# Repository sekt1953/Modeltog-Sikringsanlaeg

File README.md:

# Modeltogs Sikringsanlæg

Sikrings anlæg for modeltog med DCC system, ESPHome &amp; Home Assistant

## [Datasheet](./Project/Datasheet/README.md#datasheet)

* [CanBus](./Project/Datasheet/README.md#canbus)
  * [ESPHome](./Project/Datasheet/README.md#esphome)
  * [Kabling](./Project/Datasheet/README.md#canbus-kabling)
  * [Videos](./Project/Datasheet/Kabeling/Canbus:Videos.md)
* [DCC](./Project/Datasheet/README.md#dcc)
  * [Kabling](./Project/Datasheet/README.md#dcc-kabling)
* [KiCad](./Project/Datasheet/README.md#kicad)
  * [Track impedans](./Project/Datasheet/README.md#track-impedans)
  * [Custom Symbol and Footprints](./Project/Datasheet/README.md#custom-symbol-and-footprints)
* [Parts:](./Project/Datasheet/README.md#parts)
  * [Semiconductor](./Project/Datasheet/README.md#semiconductor)
  * [Modules](./Project/Datasheet/README.md#modules)
  * [Stik](./Project/Datasheet/README.md#stik)

## [Libraries](./Project/libraries/README.md)

* [KiCad Libraries:](./Project/libraries/KiCad/)
  * [Modules Symboler](./Project/libraries/SEKT_Modules.kicad_sym)
  * [Modules Footprint](./Project/libraries/SEKT_Modules.pretty/)
* [FreeCAD 3D Step files:](./Project/libraries/README.md)
  * [Semiconductor](./Project/libraries/README.md#semiconductor)
  * [Modules](./Project/libraries/README.md#modules)
  * [Stik](./Project/libraries/README.md#stik)

## Projekter

* [Sporbesat](./Project/Sikring/Sporbesat/README.md)
  * Detektor kredsløb
    * [Beskrivelse af Sporbesat Detektor Diagram](./Project/Sikring/Sporbesat/Detektor/Beskrivelse.md)
    * KiCad Filer:
      * [Sporbesat-Detektor](./Project/Sikring/Sporbesat/Sikring_Sporbesat/Images/Sikring_Sporbesat-Sporbesat_Sensor.svg)
  * CANBUS
    * [CanBus og HomeAssistant](./Project/CANBUS/1_CanBus_og_HomeAssistant.md)
    * [CanBus med Output og svar](./Project/CANBUS/2_CanBus_med%20_Output_og_svar.md)
  * KiCAD
  * FreeCAD
  * ESPHome
  * Home Assistant
* Sporskifte styring
* Signal styring
* test

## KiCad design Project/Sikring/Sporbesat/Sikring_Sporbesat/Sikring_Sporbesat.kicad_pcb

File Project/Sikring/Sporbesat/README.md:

# Sikringsanlæg - Sporbesat

## 4 ports sporbesat detektor kredsløb

* Detektor kredsløb
  * [Beskrivelse af Sporbesat Detektor Diagram](./Detektor/Beskrivelse.md)
  * KiCad (Schmatic & PCB) filer:
    * [Sporbesat-Detektor.kicad_pro](../../KiCad/Sporbesat-Detektor/Sporbesat-Detektor.kicad_pro)
  * FreeCAD 3D modeller af komponenter:
    * [Datasheet Parts](../../Datasheet/README.md#parts)

## Transmitter

### KiCad (Schmatic & PCB)

* [Track impedans calculater](../../Datasheet/TrackImpedansCalculater.md)

### CanBus

#### [ESP32 CAN](https://esphome.io/components/canbus/esp32_can/)

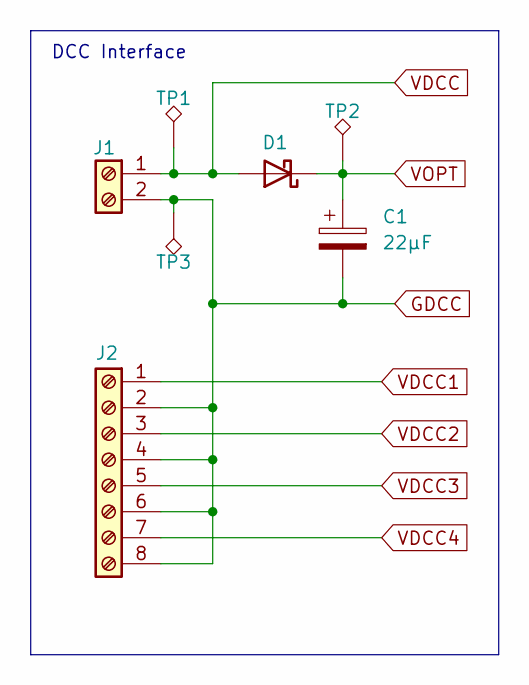
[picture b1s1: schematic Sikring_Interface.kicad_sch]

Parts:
C1: 22µF; CP_EIA-7343-43_Kemet-X
D1: Schottky, SMA, 30V, 1A; D_DO-214AC(SMA)
J1: Screw_Terminal_01x02; TerminalBlock_Phoenix_MKDS-1,5-2-5.08_1x02_P5.08mm_Horizont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
J2: Screw_Terminal_01x08; TerminalBlock_Phoenix_MKDS-1,5-8-5.08_1x08_P5.08mm_Horizont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
TP1: VDCC; TestPoint_Loop_D2.60mm_Drill1.4mm_Beaded
TP2: VOPT; TestPoint_Loop_D2.60mm_Drill1.4mm_Beaded
TP3: GDCC; TestPoint_Loop_D2.60mm_Drill1.4mm_Beaded

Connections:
GDCC: C1.2, J1.2, J2.2, J2.4, J2.6, J2.8, TP3.1 (1_1); also elsewhere on the board
VDCC: D1.2 (A), J1.1, TP1.1 (1_1); also elsewhere on the board
VDCC1: J2.1; also elsewhere on the board
VDCC2: J2.3; also elsewhere on the board
VDCC3: J2.5; also elsewhere on the board
VDCC4: J2.7; also elsewhere on the board
VOPT: C1.1, D1.1 (K), TP2.1 (1_1); also elsewhere on the board

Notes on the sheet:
DCC Interface

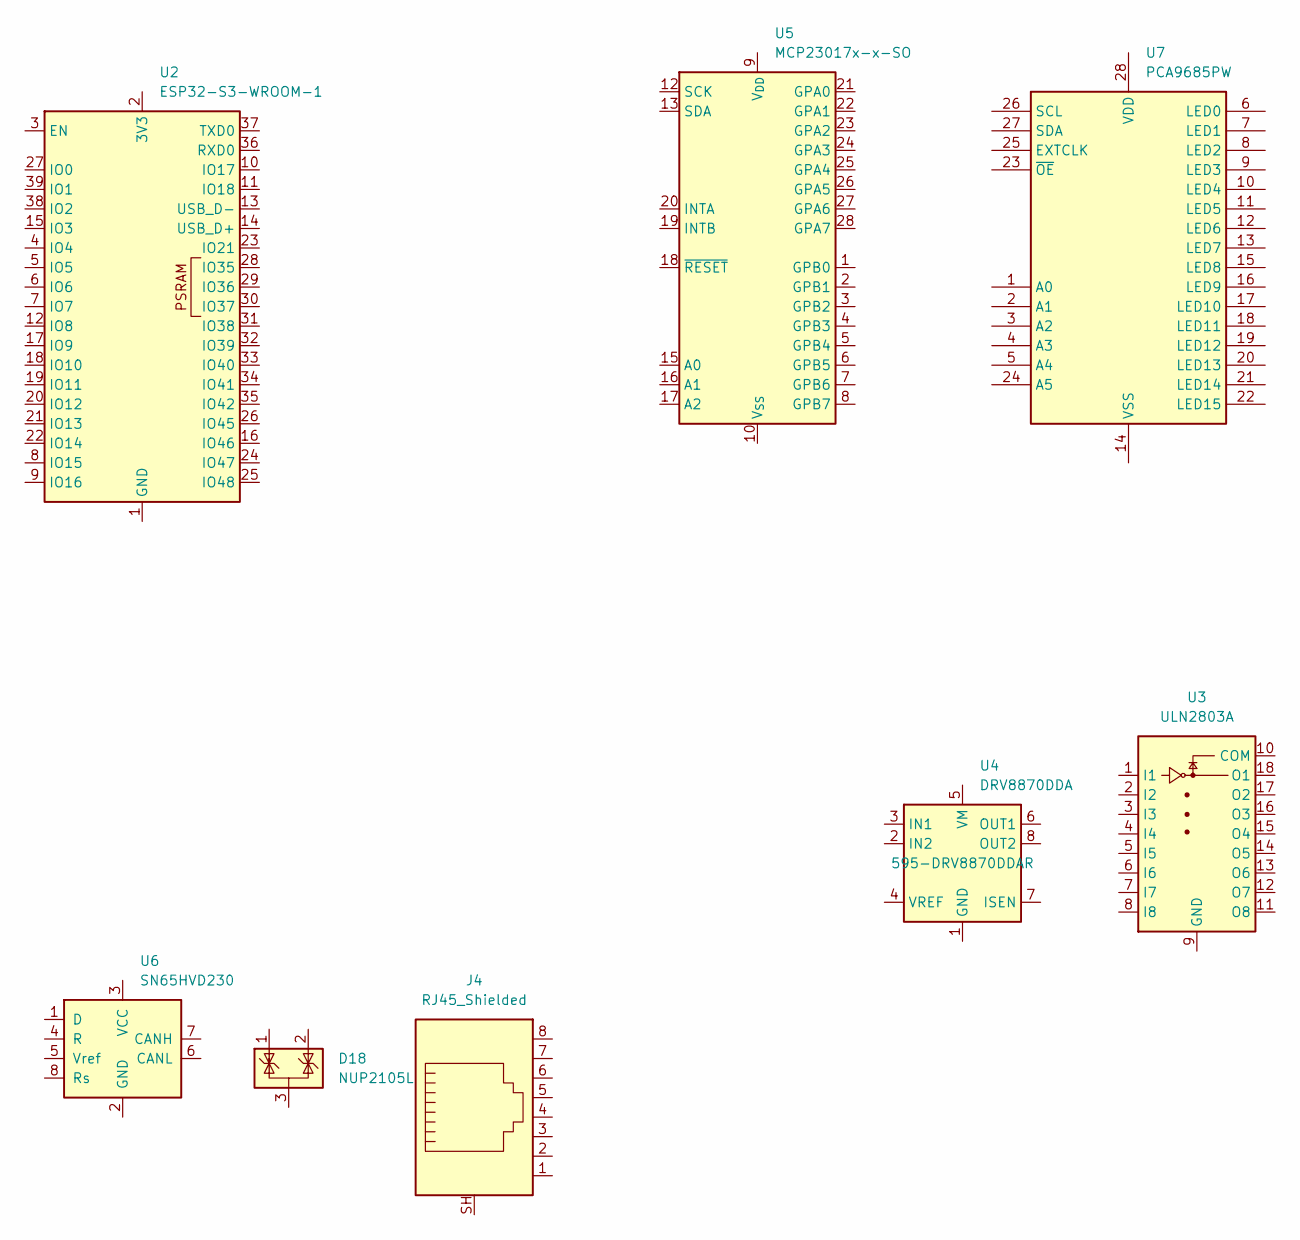
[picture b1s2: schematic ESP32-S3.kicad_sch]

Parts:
D18: NUP2105L; SOT-23; Mouser Part No 637-NUP2105L
J4: RJ45_Shielded; Mouser No: 490-CRJ009-ML4-TH
U2: ESP32-S3-WROOM-1
U3: ULN2803A; SOIC-18W_7.5x11.6mm_P1.27mm; Mouser Part No 595-ULN2803CDWR
U4: DRV8870DDA; Texas_HTSOP-8-1EP_3.9x4.9mm_P1.27mm_EP2.95x4.9mm_Mask2.4x3.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; Mouser Part No 595-DRV8870DDAR
U5: MCP23017x-x-SO; SOIC-28W_7.5x17.9mm_P1.27mm; Mouser No: 579-MCP23017-E/SO
U6: SN65HVD230; SOIC-8_3.9x4.9mm_P1.27mm; Mouser Part No 595-SN65HVD230DR
U7: PCA9685PW; TSSOP-28_4.4x9.7mm_P0.65mm; Mouser Part No 771-PCA9685PW,118

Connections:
unnamed: U2.1 (GND), U2.40 (GND), U2.41 (GND)
unnamed: U4.1 (GND), U4.9 (GND)

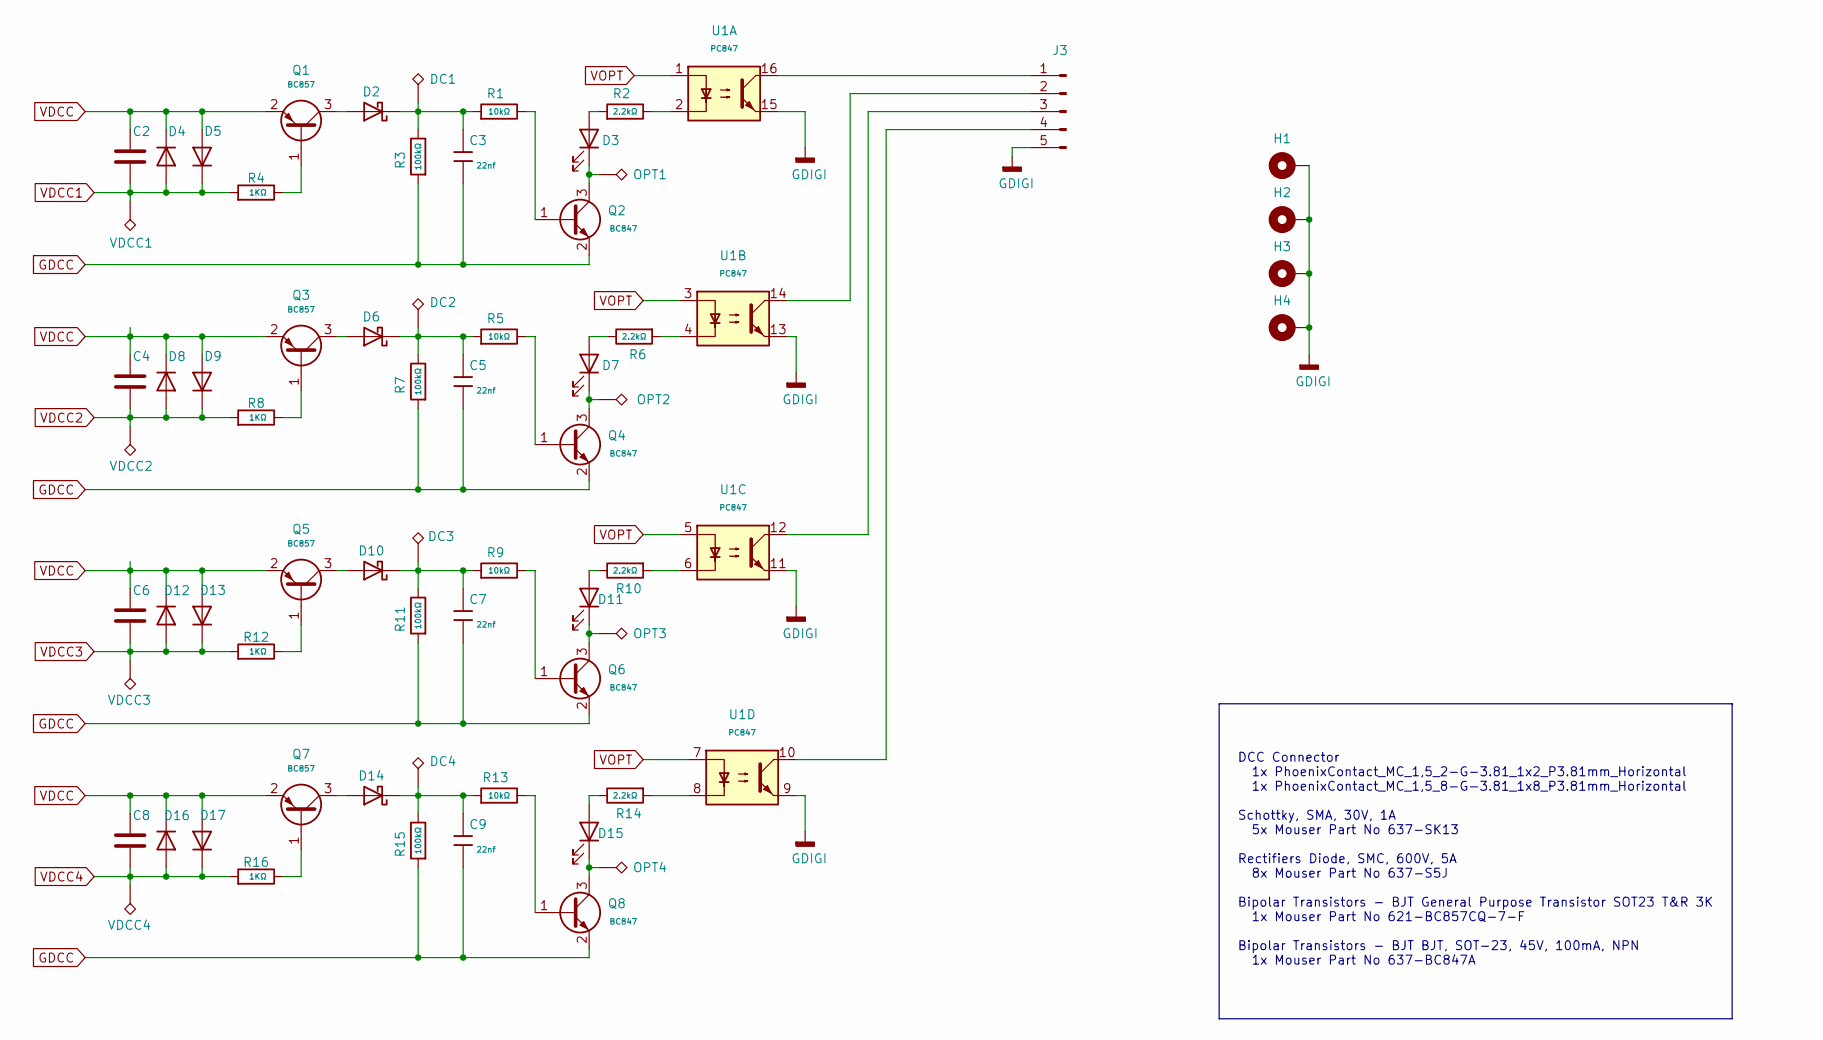
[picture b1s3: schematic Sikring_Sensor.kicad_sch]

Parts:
C2, C4, C6, C8: 100nF; C_1206_3216Metric
C3, C5, C7, C9: 22nf; C_1206_3216Metric; Voltage Rated 100V; Tolerance ±10%; Part CL21B474KBFNNNE; LCSC C13967
D2, D6, D10, D14: Schottky, SMA, 30V, 1A; D_DO-214AC(SMA)
D3, D7, D11, D15: LED; LED_0805_2012Metric
D4, D5, D8, D9, D12, D13, D16, D17: S5A; D_SMC(DO-214AB)
H1, H2, H3, H4: MountingHole_Pad; MountingHole_3.2mm_M3_Pad_TopBottom
J3: Conn_01x05_Pin; Molex_SL_171971-0005_1x05_P2.54mm_Vertical
Q1: BC857; SOT-23; Mouser No: 621-BC857CQ-7-F
Q2: BC847; SOT-23; Mouser No: Mouser No: 637-BC847A
Q3, Q5, Q7: BC857; SOT-23
Q4, Q6, Q8: BC847; SOT-23
R1, R5, R9, R13: 10kΩ; R_0805; Overload Voltage (Max) 150V; Tolerance ±1%; Part 0805W8F1801T5E; LCSC C17398
R2, R6, R10, R14: 2.2kΩ; R_0805; Overload Voltage (Max) 150V; Tolerance ±1%; Part 0805W8F1801T5E; LCSC C17398
R3, R7, R11, R15: 100kΩ; R_0805; Overload Voltage (Max) 150V; Tolerance ±1%; Part 0805W8F1801T5E; LCSC C17398
R4, R8, R12, R16: 1KΩ; R_0805; Overload Voltage (Max) 150V; Tolerance ±1%; Part 0805W8F1801T5E; LCSC C17398
TP4: DC1; TestPoint_Loop_D2.60mm_Drill1.4mm_Beaded
TP5: OPT1; TestPoint_Loop_D2.60mm_Drill1.4mm_Beaded
TP6: VDCC1; TestPoint_Loop_D2.60mm_Drill1.4mm_Beaded
TP7: DC2; TestPoint_Loop_D2.60mm_Drill1.4mm_Beaded
TP8: OPT2; TestPoint_Loop_D2.60mm_Drill1.4mm_Beaded
TP9: VDCC2; TestPoint_Loop_D2.60mm_Drill1.4mm_Beaded
TP10: DC3; TestPoint_Loop_D2.60mm_Drill1.4mm_Beaded
TP11: OPT3; TestPoint_Loop_D2.60mm_Drill1.4mm_Beaded
TP12: VDCC3; TestPoint_Loop_D2.60mm_Drill1.4mm_Beaded
TP13: DC4; TestPoint_Loop_D2.60mm_Drill1.4mm_Beaded
TP14: OPT4; TestPoint_Loop_D2.60mm_Drill1.4mm_Beaded
TP15: VDCC4; TestPoint_Loop_D2.60mm_Drill1.4mm_Beaded
U1: PC847; DIP-16_W7.62mm; Mouser No: 782-ILQ621GB-X017T

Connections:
GDCC: C3.2, C5.2, C7.2, C9.2, Q2.2 (E), Q4.2 (E), Q6.2 (E), Q8.2 (E), R3.1, R7.1, R11.1, R15.1; also elsewhere on the board
GDIGI: H1.1 (1_1), H2.1 (1_1), H3.1 (1_1), H4.1 (1_1), J3.5, U1.9, U1.11, U1.13, U1.15
unnamed: D2.2 (A), Q1.3 (C)
unnamed: C3.1, D2.1 (K), R1.1, R3.2, TP4.1 (1_1)
unnamed: D3.2 (A), R2.1
unnamed: D3.1 (K), Q2.3 (C), TP5.1 (1_1)
unnamed: D6.2 (A), Q3.3 (C)
unnamed: C5.1, D6.1 (K), R5.1, R7.2, TP7.1 (1_1)
unnamed: D7.2 (A), R6.2
unnamed: D7.1 (K), Q4.3 (C), TP8.1 (1_1)
unnamed: D10.2 (A), Q5.3 (C)
unnamed: C7.1, D10.1 (K), R9.1, R11.2, TP10.1 (1_1)
unnamed: D11.2 (A), R10.2
unnamed: D11.1 (K), Q6.3 (C), TP11.1 (1_1)
unnamed: D14.2 (A), Q7.3 (C)
unnamed: C9.1, D14.1 (K), R13.1, R15.2, TP13.1 (1_1)
unnamed: D15.2 (A), R14.2
unnamed: D15.1 (K), Q8.3 (C), TP14.1 (1_1)
unnamed: J3.1, U1.16
unnamed: J3.2, U1.14
unnamed: J3.3, U1.12
unnamed: J3.4, U1.10
unnamed: Q1.1 (B), R4.2
unnamed: Q2.1 (B), R1.2
unnamed: Q3.1 (B), R8.2
unnamed: Q4.1 (B), R5.2
unnamed: Q5.1 (B), R12.2
unnamed: Q6.1 (B), R9.2
unnamed: Q7.1 (B), R16.2
unnamed: Q8.1 (B), R13.2
unnamed: R2.2, U1.2
unnamed: R6.1, U1.4
unnamed: R10.1, U1.6
unnamed: R14.1, U1.8
VDCC: C2.1, C4.1, C6.1, C8.1, D4.1 (K), D5.2 (A), D8.1 (K), D9.2 (A), D12.1 (K), D13.2 (A), D16.1 (K), D17.2 (A), Q1.2 (E), Q3.2 (E), Q5.2 (E), Q7.2 (E); also elsewhere on the board
VDCC1: C2.2, D4.2 (A), D5.1 (K), R4.1, TP6.1 (1_1); also elsewhere on the board
VDCC2: C4.2, D8.2 (A), D9.1 (K), R8.1, TP9.1 (1_1); also elsewhere on the board
VDCC3: C6.2, D12.2 (A), D13.1 (K), R12.1, TP12.1 (1_1); also elsewhere on the board
VDCC4: C8.2, D16.2 (A), D17.1 (K), R16.1, TP15.1 (1_1); also elsewhere on the board
VOPT: U1.1, U1.3, U1.5, U1.7; also elsewhere on the board

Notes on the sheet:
DCC Connector 1x PhoenixContact_MC_1,5_2-G-3.81_1x2_P3.81mm_Horizontal 1x PhoenixContact_MC_1,5_8-G-3.81_1x8_P3.81mm_Horizontal Schottky, SMA, 30V, 1A 5x Mouser Part No 637-SK13 Rectifiers Diode, SMC, 600V, 5A 8x Mouser Part No 637-S5J Bipolar Transistors - BJT General Purpose Transistor SOT23 T&R 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

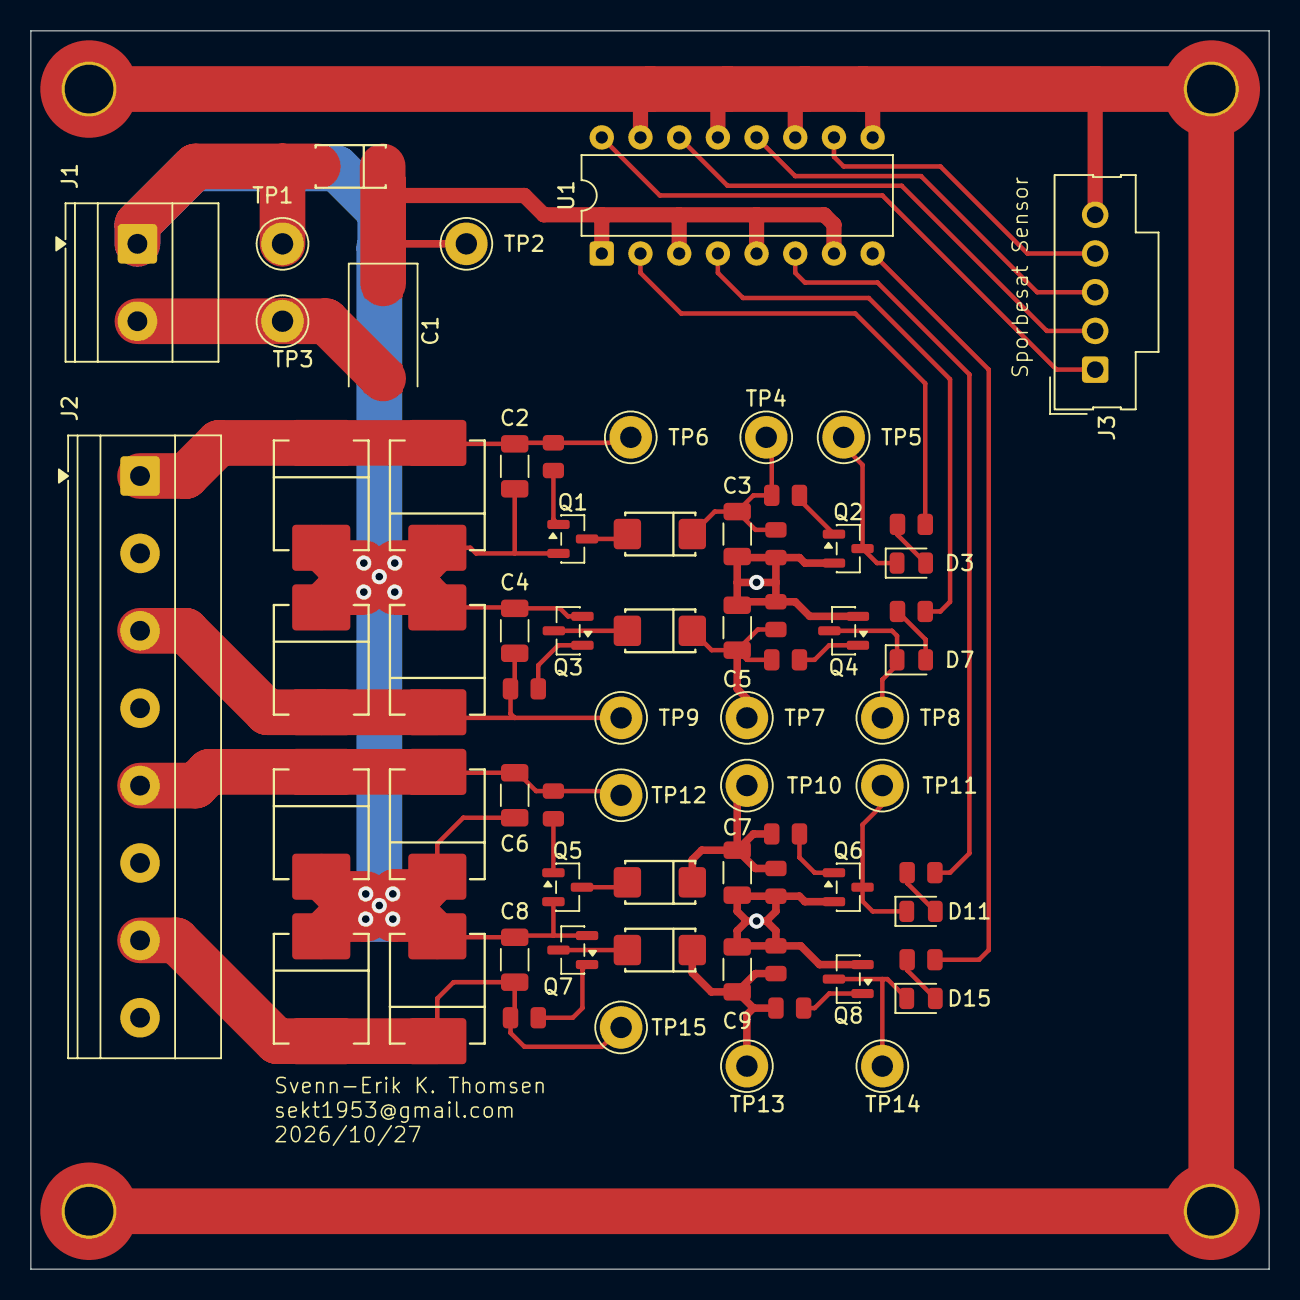
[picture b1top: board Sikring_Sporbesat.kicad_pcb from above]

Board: 2 copper layers, 81.3 x 81.3 mm, 73 parts (0 on the bottom side), 40 nets.
